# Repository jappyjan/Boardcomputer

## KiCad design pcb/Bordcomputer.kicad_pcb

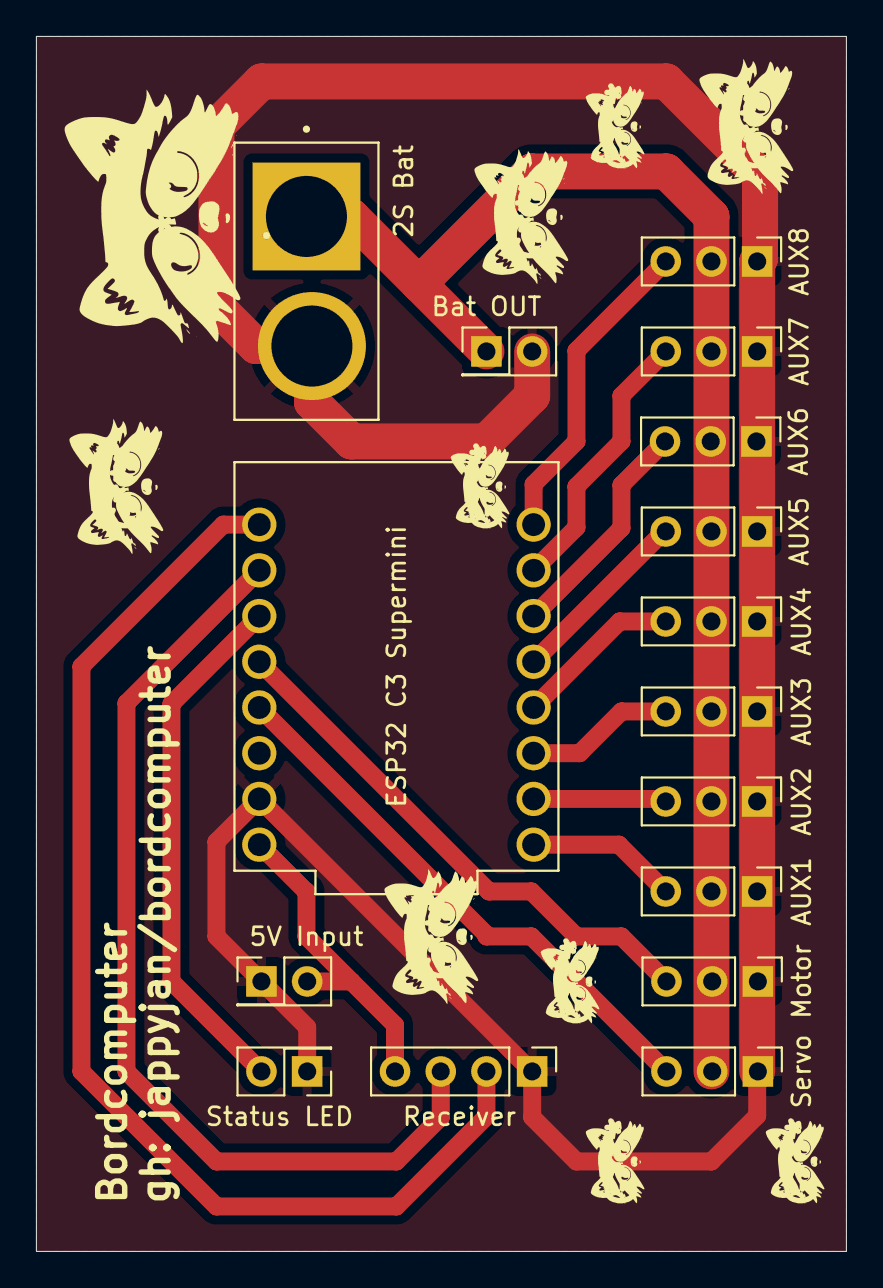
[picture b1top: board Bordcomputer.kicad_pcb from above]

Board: 2 copper layers, 45.0 x 67.5 mm, 16 parts (0 on the bottom side), 16 nets.

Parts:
2S Bat: 2S Battery; AMASS_XT60PB-M
5V Input: 5V Input; PinHeader_2x01_P2.54mm_Vertical
AUX1: AUX1; PinHeader_1x03_P2.54mm_Vertical
AUX2: AUX2; PinHeader_1x03_P2.54mm_Vertical
AUX3: AUX3; PinHeader_1x03_P2.54mm_Vertical
AUX4: AUX4; PinHeader_1x03_P2.54mm_Vertical
AUX5: AUX5; PinHeader_1x03_P2.54mm_Vertical
AUX6: AUX6; PinHeader_1x03_P2.54mm_Vertical
AUX7: AUX7; PinHeader_1x03_P2.54mm_Vertical
AUX8: AUX8; PinHeader_1x03_P2.54mm_Vertical
Bat OUT: Bat OUT; PinHeader_2x01_P2.54mm_Vertical
D5: Status LED; PinHeader_2x01_P2.54mm_Vertical
ESP32 C3 Supermini: ESP32 C3 SUPERMINI; MODULE_ESP32-C3_SUPERMINI
Motor: Motor; PinHeader_1x03_P2.54mm_Vertical
Receiver: Receiver; PinHeader_1x04_P2.54mm_Vertical
Servo: Steering; PinHeader_1x03_P2.54mm_Vertical

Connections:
+5V: 5V Input.2, ESP32 C3 Supermini.5V, Receiver.4
+BATT: 2S Bat.1 (+), AUX1.2, AUX2.2, AUX3.2, AUX4.2, AUX5.2, AUX6.2, AUX7.2, AUX8.2, Bat OUT.1, Motor.2, Servo.2
GND: 2S Bat.2 (-), 5V Input.1, AUX1.1, AUX2.1, AUX3.1, AUX4.1, AUX5.1, AUX6.1, AUX7.1, AUX8.1, Bat OUT.2, D5.1 (K), ESP32 C3 Supermini.G (GND), Motor.1, Receiver.1, Servo.1
unnamed: D5.2 (A), ESP32 C3 Supermini.2 (GPIO2)
unnamed: ESP32 C3 Supermini.0 (GPIO0), Receiver.2
unnamed: ESP32 C3 Supermini.1 (GPIO1), Receiver.3
unnamed: ESP32 C3 Supermini.3 (GPIO3), Motor.3
unnamed: ESP32 C3 Supermini.4 (GPIO4), Servo.3
unnamed: AUX1.3, ESP32 C3 Supermini.5 (GPIO5)
unnamed: AUX2.3, ESP32 C3 Supermini.6 (GPIO6)
unnamed: AUX3.3, ESP32 C3 Supermini.7 (GPIO7)
unnamed: AUX4.3, ESP32 C3 Supermini.8 (GPIO8)
unnamed: AUX5.3, ESP32 C3 Supermini.9 (GPIO9)
unnamed: AUX6.3, ESP32 C3 Supermini.10 (GPIO10)
unnamed: AUX7.3, ESP32 C3 Supermini.20 (GPIO20)
unnamed: AUX8.3, ESP32 C3 Supermini.21 (GPIO21)

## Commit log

2025-02-01 feat: everything works
2025-02-01 feat: kicad pcb files
2025-02-07 working, now with ms for servos
2025-02-09 complete web configurator
2025-02-09 cleanup old config before setting new config
2025-02-10 Way too much stuff for one commit... essentially made everything configurable through a web ui
2025-02-12 chore: fix typo and rename Boardcomputer to Bordcomputer
